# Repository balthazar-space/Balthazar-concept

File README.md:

# Balthazar

Open-hardware laptop computer modules description and concept.

These are electronic schematic modules as presented at https://balthazar.space/wiki/Balthazar
with the main aim for team access.

We are building it from periphery - inwards.

## Repositories

### BalthazarPSU

[BalthazarPSU](https://github.com/balthazar-space/balthazarPSU3) is a combined battery charger, buck-boost coverter and stereo power amplifier.

Previous versions:
   - [Version 2](https://github.com/balthazar-space/balthazarPSU2)
   - [Version 1](https://github.com/balthazar-space/balthazarPSU)

### BalthazarKeyboard
[BalthazarKeyboard](https://github.com/balthazar-space/balthazarKeyboard3) is a somewhat simplified ergonomic computer keyboard with a "diy" approach. The second iteration of the updated keyboard has some more geometric consistency. The third version adds OLED support and a menu for password protecting bootup and choosing a boot target (actual booting is still WIP).

QMK based firmware can be found in [BalthazarKeyboardQMK](https://github.com/balthazar-space/balthazarKeyboardQMK)

Previous versions:
   - [Version 2](https://github.com/balthazar-space/balthazarKeyboard2)
   - [Version 1](https://github.com/balthazar-space/balthazarKeyboard)

### BalthazarIO
[BalthazarIO](https://github.com/balthazar-space/balthazarIO) is a simple USB2.0 four-port hub for the internal devices:
   keyboard and touchpad (optional trackpad), webcam and optional audiocard.

### Case and design

[Case and design](https://github.com/balthazar-space/case-and-design) contains drawings, in DXF, DWG and STL formats.

### Unifying-PCB

[Unifying-PCB](https://github.com/balthazar-space/Unifying-PCB) is a single PCB solution for connecting the three previously designed Balthazar modules (I/O, power supply, USB 2.0, 3.0 controllers, keyboard and adding Compute Module compatible FPGA boards. 

## Prototype

So, far no prototype was built yet - these are preliminary files to be checked in practise, however the progress and pictures of the first pre-prototype are to be seen on our https://balthazar.space website under the News and Specifications and all over (also, many pretty pictures there and user-case scenarios).

Some philosophy is in the .pdf files included. The newest is [.pdf number 3](./Balthazar_System03.pdf).

## License

All resources licensed under the CERN Open Hardware Licence CERN-OHL W V.2.0

Version 2.0 of the CERN-OHL introduces three variants of the licence – strongly (S) reciprocal, weakly (W) reciprocal and permissive (P) – which aim to address specific constraints caused by different collaboration models currently used in open-hardware projects. 

The first two variants mean that if any product is made using an open hardware design, the design of that product, including any improvements or modifications, should be made available under the same licence as that of the original product. Permissive licences do not impose this condition.

See the [LICENSE.md](./LICENSE.md) file for more information.

## Funding

This project is funded through the [NGI Zero Entrust Fund](https://nlnet.nl/entrust), a fund
established by [NLnet](https://nlnet.nl) with financial support from the European Commission's
[Next Generation Internet](https://ngi.eu) program. Learn more on the [NLnet project page](https://nlnet.nl/project/Balthazar-Casing/).

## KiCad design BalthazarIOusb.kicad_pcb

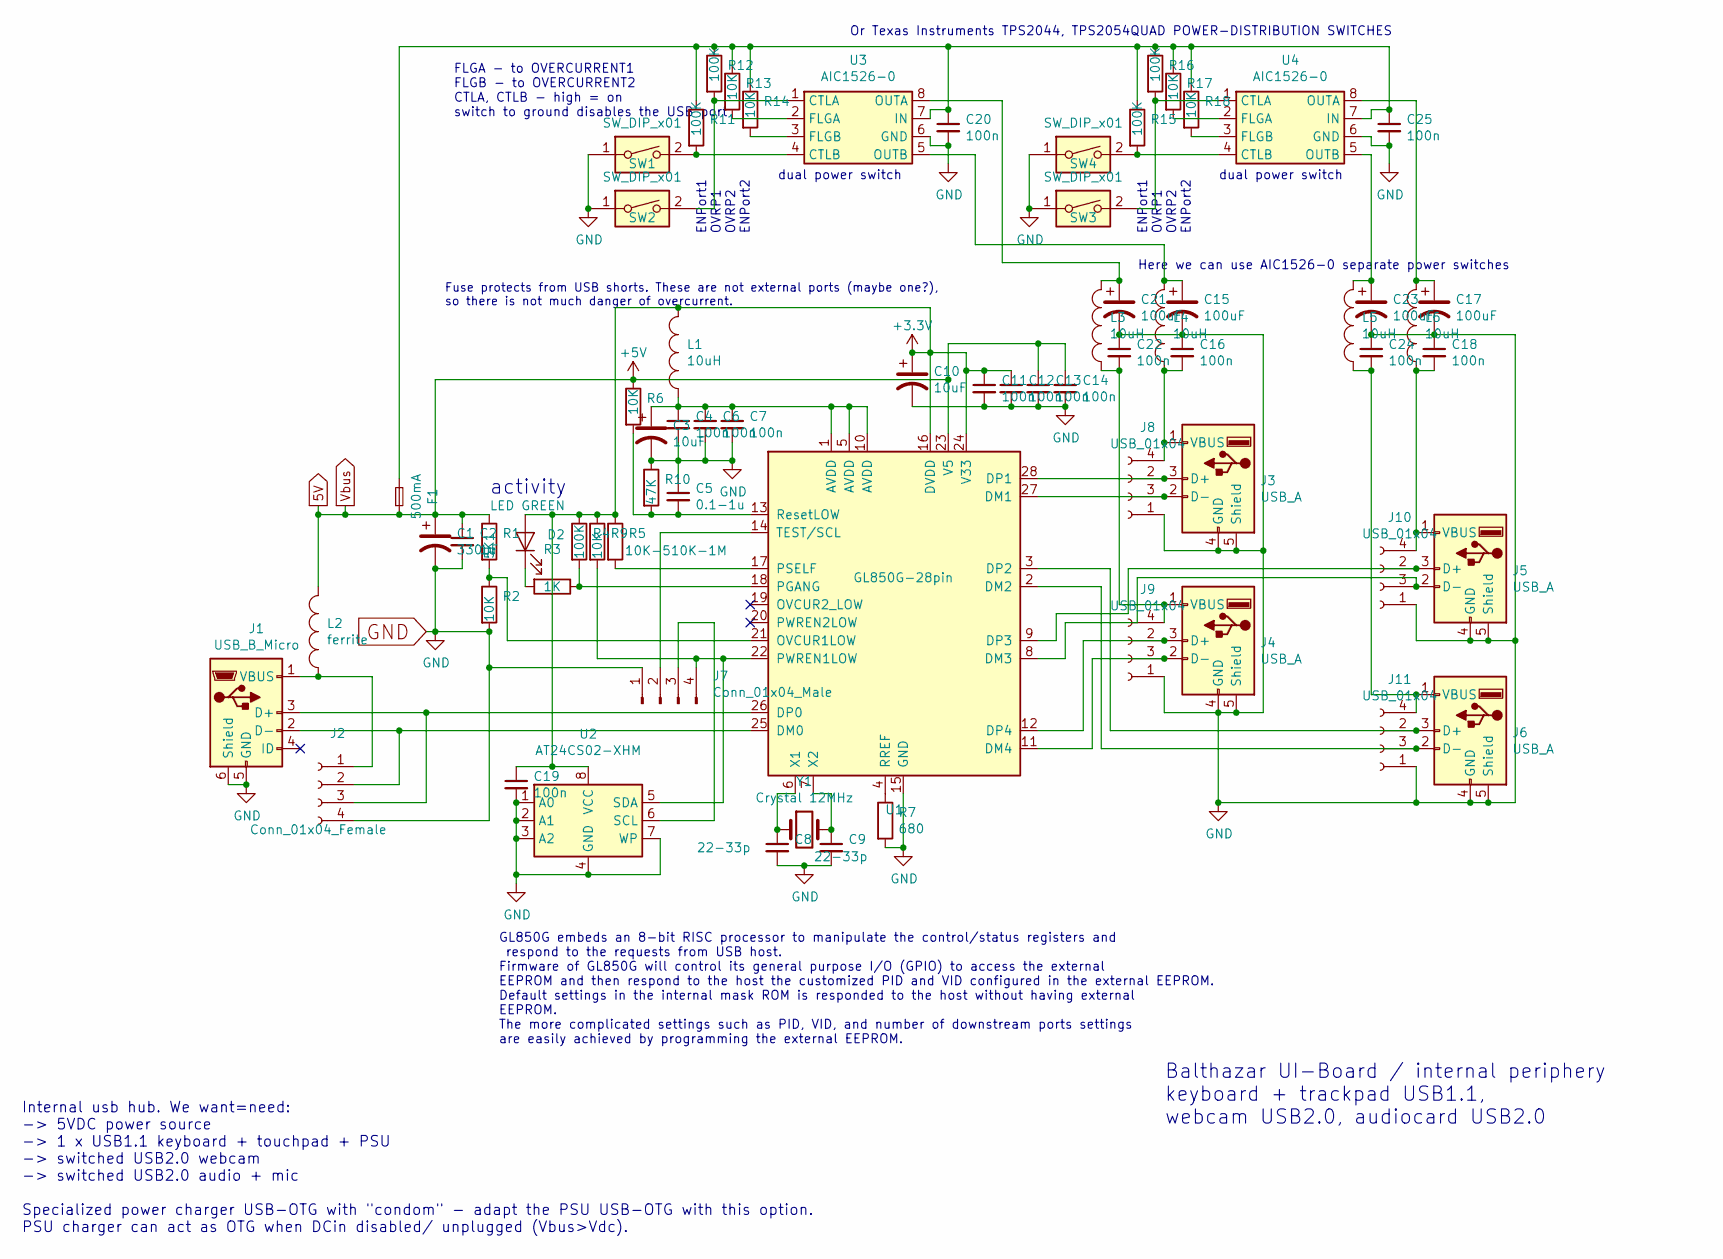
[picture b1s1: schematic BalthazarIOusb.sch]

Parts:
C1: 330uF; CP_Radial_D8.0mm_P2.50mm
C2: 1u; C_1206_3216Metric
C3, C10: 10uF; C_1206_3216Metric
C4, C6, C7, C11, C12, C13, C14, C16, C18, C19, C20, C22, C24, C25: 100n; C_1206_3216Metric
C5: 0.1-1u; C_1206_3216Metric
C8, C9: 22-33p; C_1206_3216Metric
C15, C17, C21, C23: 100uF; CP_Radial_D6.3mm_P2.50mm
D2: LED GREEN; LED_1206_3216Metric
F1: 500mA; Fuse_1206_3216Metric
J1: USB_B_Micro; USB_Micro-AB_Molex_47590-0001
J2: Conn_01x04_Female; PinSocket_1x04_P2.54mm_Horizontal
J3, J4, J5, J6: USB_A; USB_A_CNCTech_1001-011-01101_Horizontal
J7: Conn_01x04_Male; PinHeader_1x04_P2.54mm_Horizontal
J8, J9, J10, J11: USB_01x04; PinSocket_1x04_P2.54mm_Horizontal
L1, L3, L4, L5, L6: 10uH; L_1206_3216Metric
L2: ferrite; L_1206_3216Metric
R1: 5K1; R_1206_3216Metric
R2, R6, R9, R13, R14, R17, R18: 10K; R_1206_3216Metric
R3: 1K; R_1206_3216Metric
R4, R11, R12, R15, R16: 100K; R_1206_3216Metric
R5: 10K-510K-1M; R_1206_3216Metric
R7: 680; R_1206_3216Metric
R10: 47K; R_1206_3216Metric
SW1, SW2, SW3, SW4: SW_DIP_x01; SW_DIP_SPSTx01_Slide_9.78x4.72mm_W7.62mm_P2.54mm
U1: GL850G-28pin; SSOP-28_5.3x10.2mm_P0.65mm
U2: AT24CS02-XHM; SOP-8_3.9x4.9mm_P1.27mm
U3, U4: AIC1526-0; SOP-8_3.9x4.9mm_P1.27mm
Y1: Crystal 12MHz; Crystal_HC50_Vertical

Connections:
5V: C1.1, C2.1, C13.1, C14.1, F1.1, L2.2, R1.1, R6.1, U1.23 (V5)
+3V3: C10.1, C11.1, C12.1, C19.1, D2.2 (A), L1.2, R4.1, R5.1, R9.1, U1.16 (DVDD), U1.24 (V33), U2.8 (VCC)
GND: C1.2, C2.2, C3.2, C4.2, C5.1, C6.2, C7.2, C8.2, C9.2, C10.2, C11.2, C12.2, C13.2, C14.2, C15.2, C16.1, C17.2, C18.1, C19.2, C20.2, C21.2, C22.1, C23.2, C24.1, C25.2, J1.5 (GND), J1.6 (Shield), J2.4, J3.4 (GND), J3.5 (Shield), J4.4 (GND), J4.5 (Shield), J5.4 (GND), J5.5 (Shield), J6.4 (GND), J6.5 (Shield), J7.1, J8.1 (Vbus), J9.1 (Vbus), J10.1 (Vbus), J11.1 (Vbus), R2.2, R7.2, R10.1, SW1.1, SW2.1, SW3.1, SW4.1, U1.15 (GND), U2.1 (A0), U2.2 (A1), U2.3 (A2), U2.4 (GND), U2.7 (WP), U3.6 (GND), U4.6 (GND)
unnamed: C3.1, C4.1, C6.1, C7.1, L1.1, U1.1 (AVDD), U1.5 (AVDD), U1.10 (AVDD)
unnamed: C5.2, R6.2, R10.2, U1.13 (ResetLOW)
unnamed: C8.1, U1.6 (X1), Y1.1
unnamed: C9.1, U1.7 (X2), Y1.2
unnamed: C15.1, L4.2, U3.5 (OUTB)
unnamed: C16.2, J3.1 (VBUS), J8.4 (gnd), L4.1
unnamed: C17.1, L6.2, U4.8 (OUTA)
unnamed: C18.2, J5.1 (VBUS), J10.4 (gnd), L6.1
unnamed: C20.1, C25.1, F1.2, R11.1, R12.1, R13.1, R14.1, R15.1, R16.1, R17.1, R18.1, U3.7 (IN), U4.7 (IN)
unnamed: C21.1, L3.2, U3.8 (OUTA)
unnamed: C22.2, J4.1 (VBUS), J9.4 (gnd), L3.1
unnamed: C23.1, L5.2, U4.5 (OUTB)
unnamed: C24.2, J6.1 (VBUS), J11.4 (gnd), L5.1
unnamed: D2.1 (K), R3.2
unnamed: J1.1 (VBUS), J2.1, L2.1
unnamed: J1.2 (D-), J2.2, U1.25 (DM0)
unnamed: J1.3 (D+), J2.3, U1.26 (DP0)
unnamed: J3.2 (D-), J8.3, U1.27 (DM1)
unnamed: J3.3 (D+), J8.2, U1.28 (DP1)
unnamed: J4.2 (D-), J9.3, U1.11 (DM4)
unnamed: J4.3 (D+), J9.2, U1.12 (DP4)
unnamed: J7.2, U1.14 (TEST/SCL)
unnamed: J7.3, U2.6 (SCL)
unnamed: J7.4, R9.2, U1.22 (PWREN1LOW), U2.5 (SDA)
unnamed: J5.3 (D+), J10.2, U1.9 (DP3)
unnamed: J5.2 (D-), J10.3, U1.8 (DM3)
unnamed: J6.3 (D+), J11.2, U1.3 (DP2)
unnamed: J6.2 (D-), J11.3, U1.2 (DM2)
unnamed: R1.2, R2.1, U1.21 (OVCUR1LOW)
unnamed: R3.1, R4.2, U1.18 (PGANG)
unnamed: R5.2, U1.17 (PSELF)
unnamed: R7.1, U1.4 (RREF)
unnamed: R11.2, SW1.2, U3.4 (CTLB)
unnamed: R12.2, SW2.2, U3.1 (CTLA)
unnamed: R13.2, U3.2 (FLGA)
unnamed: R14.2, U3.3 (FLGB)
unnamed: R15.2, SW4.2, U4.4 (CTLB)
unnamed: R16.2, SW3.2, U4.1 (CTLA)
unnamed: R17.2, U4.2 (FLGA)
unnamed: R18.2, U4.3 (FLGB)

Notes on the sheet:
Balthazar UI-Board / internal periphery keyboard + trackpad USB1.1, webcam USB2.0, audiocard USB2.0
Fuse protects from USB shorts. These are not external ports (maybe one?), so there is not much danger of overcurrent.
activity
Internal usb hub. We want=need: -> 5VDC power source -> 1 x USB1.1 keyboard + touchpad + PSU -> switched USB2.0 webcam -> switched USB2.0 audio + mic Specialized power charger USB-OTG with "condom" - adapt the PSU USB-OTG with this option. PSU charger can act as OTG when DCin disabled/ unplugged (V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
Here we can use AIC1526-0 separate power switches
ENPort1 OVRP1 OVRP2 ENPort2
dual power switch
Or Texas Instruments TPS2044, TPS2054QUAD POWER-DISTRIBUTION SWITCHES
FLGA - to OVERCURRENT1 FLGB - to OVERCURRENT2 CTLA, CTLB - high = on switch to ground disables the USB port
GL850G embeds an 8-bit RISC processor to manipulate the control/status registers and respond to the requests from USB host. Firmware of GL850G will control its general purpose I/O (GPIO) to access the external EEPROM and then respond to the host the customized PID and VID configured in the external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

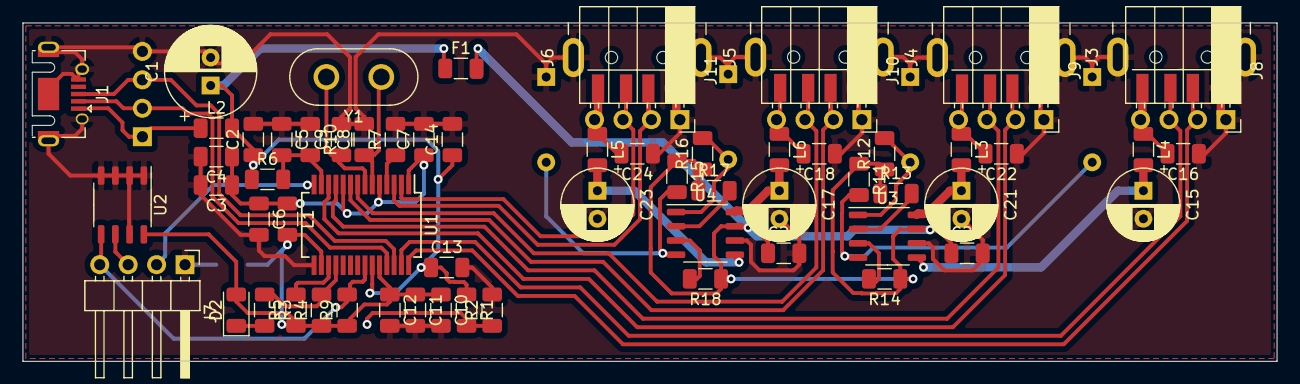
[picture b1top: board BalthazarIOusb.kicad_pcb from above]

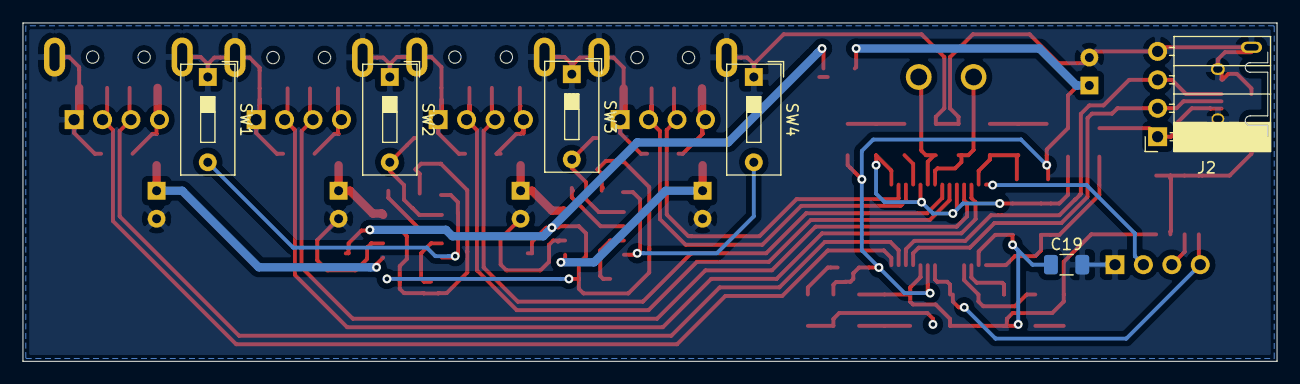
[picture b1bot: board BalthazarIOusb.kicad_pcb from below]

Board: 2 copper layers, 112.0 x 30.2 mm, 70 parts (6 on the bottom side), 43 nets.

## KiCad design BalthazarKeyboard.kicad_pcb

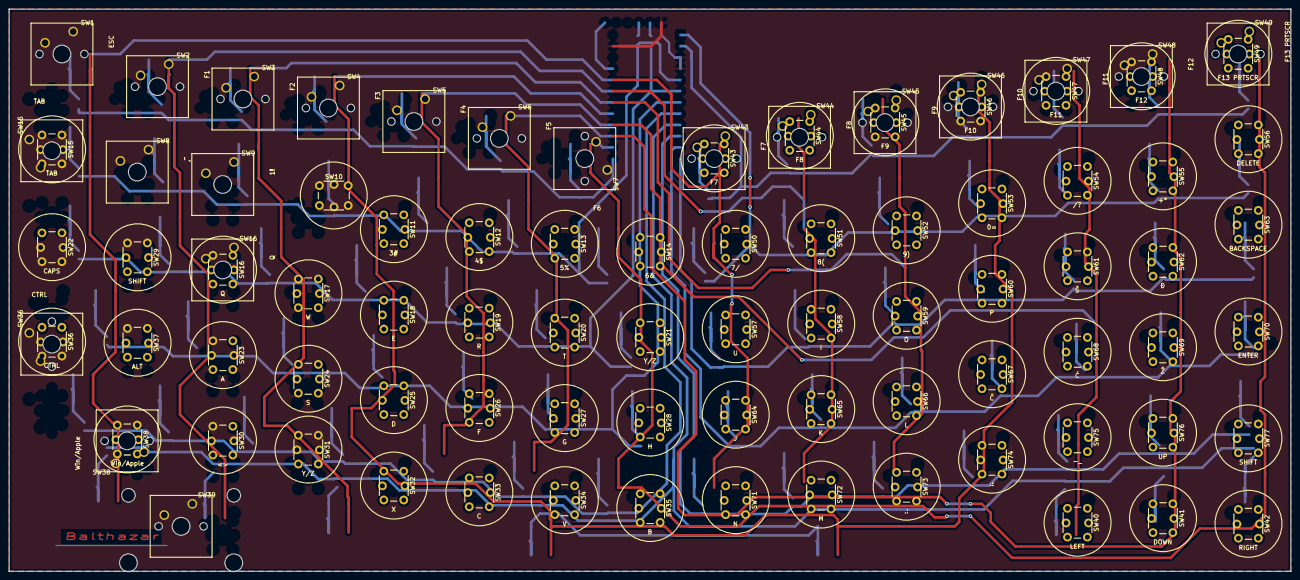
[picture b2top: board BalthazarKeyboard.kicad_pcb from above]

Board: 2 copper layers, 289.6 x 127.0 mm, 88 parts (0 on the bottom side), 18 nets.

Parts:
SW1: ESC; SW_Cherry_MX_1.25u_PCB
SW2: F1; SW_Cherry_MX_1.00u_PCB
SW3: F2; SW_Cherry_MX_1.00u_PCB
SW4: F3; SW_Cherry_MX_1.00u_PCB
SW5: F4; SW_Cherry_MX_1.00u_PCB
SW6: F5; SW_Cherry_MX_1.00u_PCB
SW7: F6; SW_Cherry_MX_1.00u_PCB
SW8: ¸¨; SW_Cherry_MX_1.00u_Plate
SW9: 1!; SW_Cherry_MX_1.00u_Plate
SW10: 2; SW_Cherry_MX_1.00u_Plate
SW11: 3#; SW_PUSH_6mm_8mm
SW12: 4$; SW_PUSH_6mm_8mm
SW13: 5%; SW_PUSH_6mm_8mm
SW14: 6&; SW_PUSH_6mm_8mm
SW15: TAB; SW_Cherry_MX_1.25u_Plate
SW15#2: TAB; SW_PUSH_6mm_8mm
SW16: Q; SW_Cherry_MX_1.00u_Plate
SW16#2: Q; SW_PUSH_6mm_8mm
SW17: W; SW_PUSH_6mm_8mm
SW18: E; SW_PUSH_6mm_8mm
SW19: R; SW_PUSH_6mm_8mm
SW20: T; SW_PUSH_6mm_8mm
SW21, SW31: Y/Z; SW_PUSH_6mm_8mm
SW22: CAPS; SW_PUSH_6mm_8mm
SW23: A; SW_PUSH_6mm_8mm
SW24: S; SW_PUSH_6mm_8mm
SW25: D; SW_PUSH_6mm_8mm
SW26: F; SW_PUSH_6mm_8mm
SW27: G; SW_PUSH_6mm_8mm
SW28: H; SW_PUSH_6mm_8mm
SW29, SW77: SHIFT; SW_PUSH_6mm_8mm
SW30: <>; SW_PUSH_6mm_8mm
SW32: X; SW_PUSH_6mm_8mm
SW33: C; SW_PUSH_6mm_8mm
SW34: V; SW_PUSH_6mm_8mm
SW35: B; SW_PUSH_6mm_8mm
SW36: CTRL; SW_Cherry_MX_1.25u_PCB
SW36#2: CTRL; SW_PUSH_6mm_8mm
SW37: ALT; SW_PUSH_6mm_8mm
SW38: Win/Apple; SW_Cherry_MX_1.25u_PCB
SW38#2: Win/Apple; SW_PUSH_6mm_8mm
SW39: SPACE; SW_Cherry_MX_2.00u_PCB
SW40: LEFT; SW_PUSH_6mm_8mm
SW41: DOWN; SW_PUSH_6mm_8mm
SW42: RIGHT; SW_PUSH_6mm_8mm
SW43: F7; SW_Cherry_MX_1.00u_PCB
SW43#2: F7; SW_PUSH_6mm_8mm
SW44: F8; SW_Cherry_MX_1.00u_PCB
SW44#2: F8; SW_PUSH_6mm_8mm
SW45: F9; SW_Cherry_MX_1.00u_PCB
SW45#2: F9; SW_PUSH_6mm_8mm
SW46: F10; SW_Cherry_MX_1.00u_PCB
SW46#2: F10; SW_PUSH_6mm_8mm
SW47: F11; SW_Cherry_MX_1.00u_PCB
SW47#2: F11; SW_PUSH_6mm_8mm
SW48: F12; SW_Cherry_MX_1.00u_PCB
SW48#2: F12; SW_PUSH_6mm_8mm
SW49: F13 PRTSCR; SW_Cherry_MX_1.25u_PCB
SW49#2: F13 PRTSCR; SW_PUSH_6mm_8mm
SW50: 7/; SW_PUSH_6mm_8mm
SW51: 8(; SW_PUSH_6mm_8mm
SW52: 9); SW_PUSH_6mm_8mm
SW53: 0=; SW_PUSH_6mm_8mm
SW54: /?; SW_PUSH_6mm_8mm
SW55: +*; SW_PUSH_6mm_8mm
SW56: DELETE; SW_PUSH_6mm_8mm
SW57: U; SW_PUSH_6mm_8mm
SW58: I; SW_PUSH_6mm_8mm
SW59: O; SW_PUSH_6mm_8mm
SW60: P; SW_PUSH_6mm_8mm
SW61: Š; SW_PUSH_6mm_8mm
SW62: Đ; SW_PUSH_6mm_8mm
SW63: BACKSPACE; SW_PUSH_6mm_8mm
SW64: J; SW_PUSH_6mm_8mm
SW65: K; SW_PUSH_6mm_8mm
SW66: L; SW_PUSH_6mm_8mm
SW67: Č; SW_PUSH_6mm_8mm
SW68: Ć; SW_PUSH_6mm_8mm
SW69: Ž; SW_PUSH_6mm_8mm
SW70: ENTER; SW_PUSH_6mm_8mm
SW71: N; SW_PUSH_6mm_8mm
SW72: M; SW_PUSH_6mm_8mm
SW73: ,;; SW_PUSH_6mm_8mm
SW74: .:; SW_PUSH_6mm_8mm
SW75: -_; SW_PUSH_6mm_8mm
SW76: UP; SW_PUSH_6mm_8mm

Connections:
unnamed: SW15.2, SW15#2.2
unnamed: SW16.2, SW16#2.2
unnamed: SW36.2, SW36#2.2
unnamed: SW38.2, SW38#2.2
unnamed: SW43.2, SW43#2.2
unnamed: SW44.2, SW44#2.2
unnamed: SW45.2, SW45#2.2
unnamed: SW46.2, SW46#2.2
unnamed: SW47.2, SW47#2.2
unnamed: SW48.2, SW48#2.2
unnamed: SW49.2, SW49#2.2
row1: SW1.1, SW8.1, SW15.1, SW15#2.1, SW22.1, SW29.1, SW36.1, SW36#2.1, SW43.1, SW43#2.1, SW50.1, SW57.1, SW64.1, SW71.1
row2: SW2.1, SW9.1, SW16.1, SW16#2.1, SW23.1, SW30.1, SW37.1, SW44.1, SW44#2.1, SW51.1, SW58.1, SW65.1, SW72.1
row3: SW3.1, SW10.1, SW17.1, SW24.1, SW31.1, SW38.1, SW38#2.1, SW45.1, SW45#2.1, SW52.1, SW59.1, SW66.1, SW73.1
row4: SW4.1, SW11.1, SW18.1, SW25.1, SW32.1, SW39.1, SW46.1, SW46#2.1, SW53.1, SW60.1, SW67.1, SW74.1
row5: SW5.1, SW12.1, SW19.1, SW26.1, SW33.1, SW40.1, SW47.1, SW47#2.1, SW54.1, SW61.1, SW68.1, SW75.1
row6: SW6.1, SW13.1, SW20.1, SW27.1, SW34.1, SW41.1, SW48.1, SW48#2.1, SW55.1, SW62.1, SW69.1, SW76.1
row7: SW7.1, SW14.1, SW21.1, SW28.1, SW35.1, SW42.1, SW49.1, SW49#2.1, SW56.1, SW63.1, SW70.1, SW77.1

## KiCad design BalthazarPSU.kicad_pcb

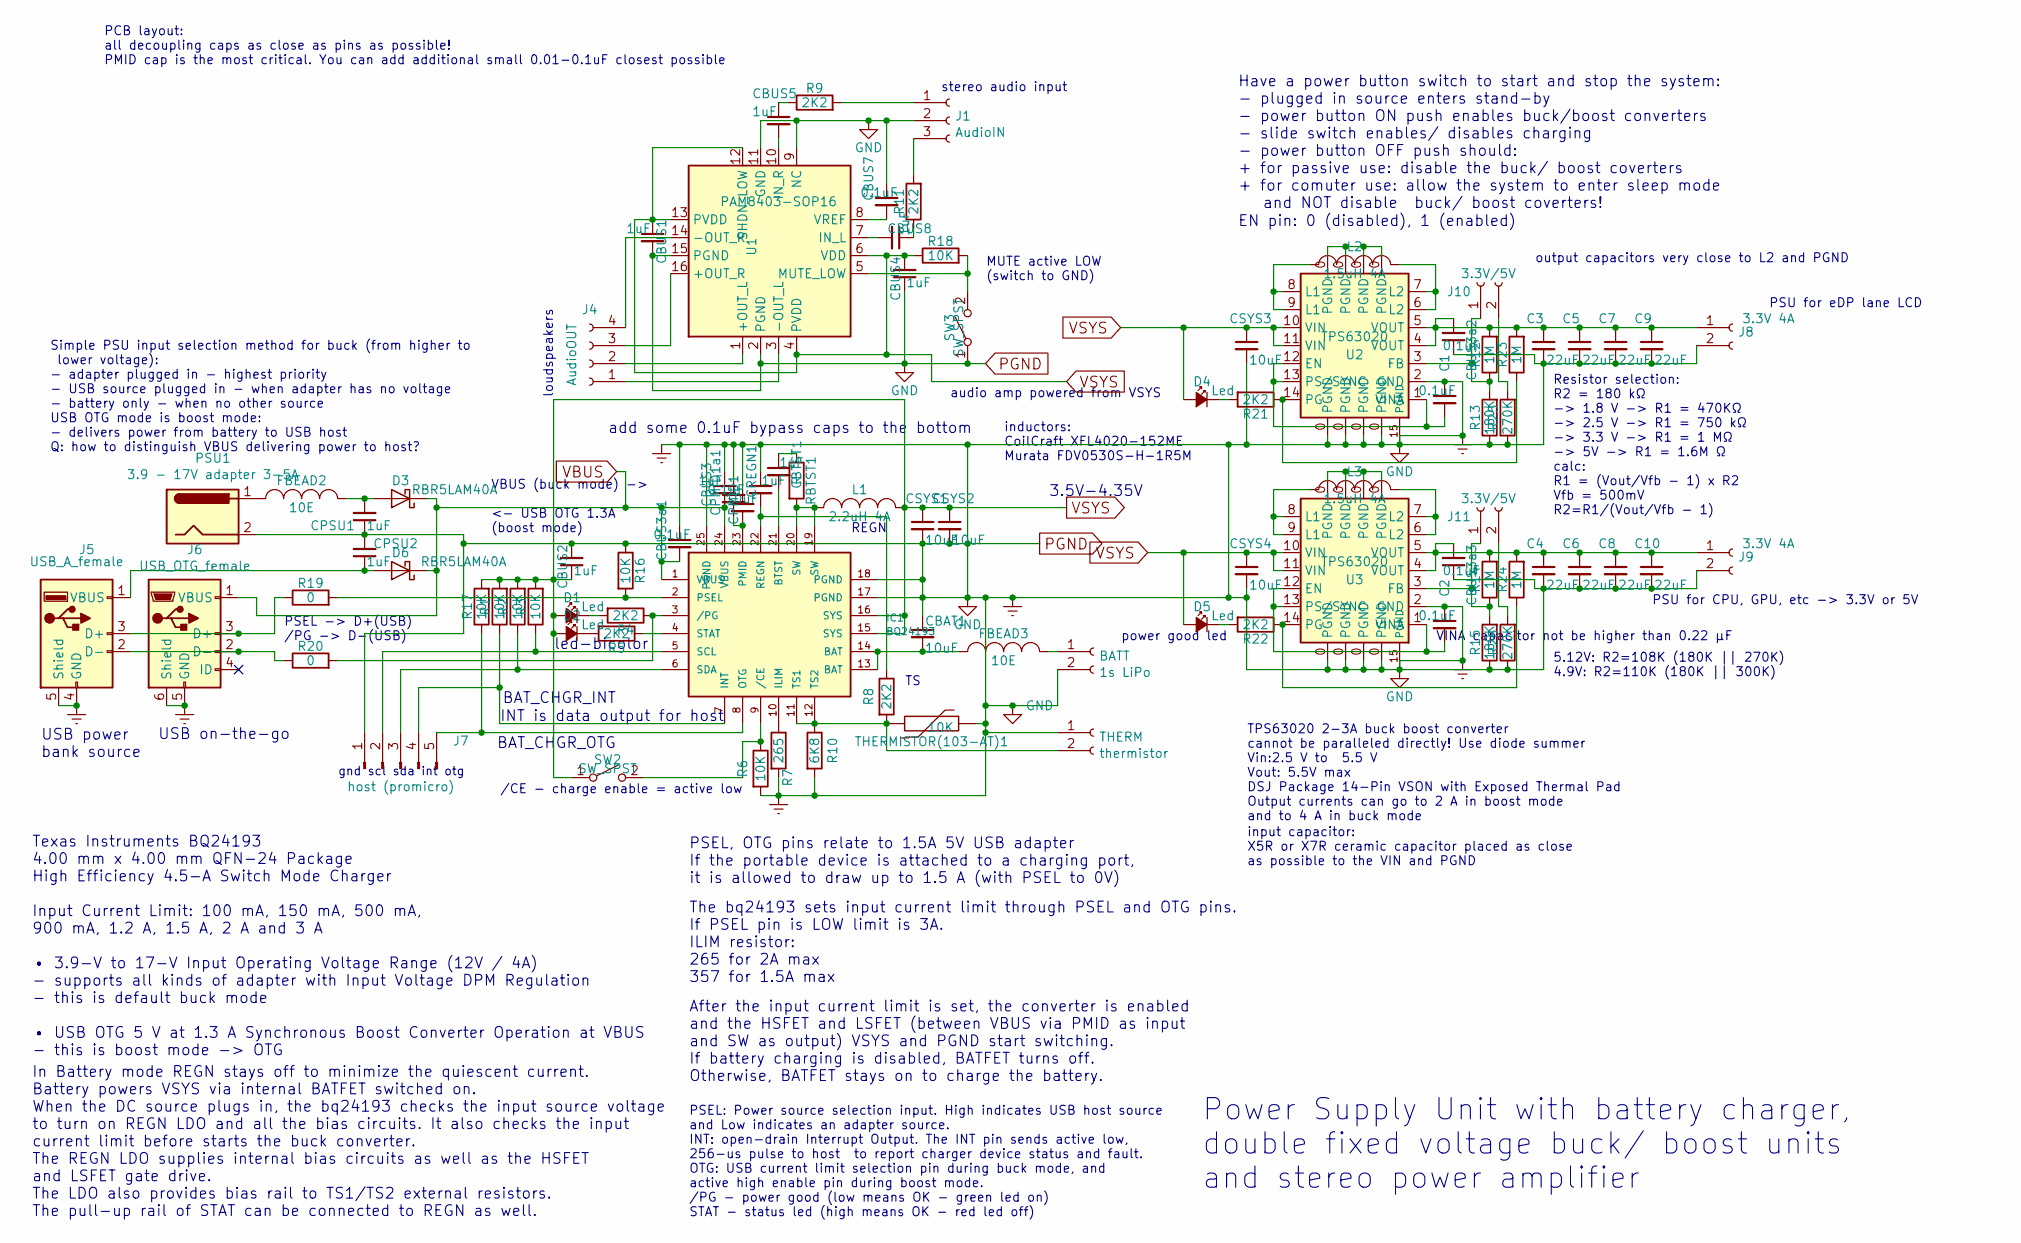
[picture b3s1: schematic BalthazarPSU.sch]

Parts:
BATT: 1s LiPo; TerminalBlock_bornier-2_P5.08mm
C1, C2: 0.1uF; C_1206_3216Metric
C3, C4, C5, C6, C7, C8, C9, C10: 22uF; C_1206_3216Metric
CBAT1: 10uF; C_1206_3216Metric
CBTST1: 1uF; C_1206_3216Metric
CBUS1, CBUS2, CBUS3, CBUS4, CBUS5, CBUS8: 1uF; C_1206_3216Metric
CBUS3a1, CBUS3a2, CBUS3a3: 0.1uF; C_0805_2012Metric
CBUS7: 0.1uF; C_1206_3216Metric
CPMID1: 10uF; C_1206_3216Metric
CPMID1a1: 0.1uF; C_0805_2012Metric
CPSU1, CPSU2: 1uF; C_1206_3216Metric
CREGN1: 1uF; C_1206_3216Metric
CSYS1, CSYS2, CSYS3, CSYS4: 10uF; C_1206_3216Metric
D1, D2, D4, D5: Led; LED_1206_3216Metric
D3, D6: RBR5LAM40A; D_SOD-128
FBEAD2, FBEAD3: 10E; L_Neosid_MicroCoil_Ms36-L
IC1: BQ24193; QFN-24-1EP_4x4mm_P0.5mm_EP2.7x2.7mm_ThermalVias
J1: AudioIN; PinSocket_1x03_P2.54mm_Horizontal
J4: AudioOUT; PinSocket_1x04_P2.54mm_Horizontal
J5: USB_A_female; USB_A_CNCTech_1001-011-01101_Horizontal-Female
J6: USB_OTG_female; USB_Micro-B_Molex-105133-0031
J7: host (promicro); PinHeader_1x06_P2.54mm_Horizontal
J8, J9: 3.3V 4A; TerminalBlock_bornier-2_P5.08mm
J10, J11: 3.3V/5V; TestPoint_2Pads_Pitch2.54mm_Drill0.8mm
L1: 2.2uH 4A; L_Coilcraft_XxL4020
L2, L3: 1.5uH 4A; L_Coilcraft_XxL4020
PSU1: 3.9 - 17V adapter 3-5A; TerminalBlock_bornier-2_P5.08mm
R1, R2, R3, R6, R16, R17, R18: 10K; R_1206_3216Metric
R4, R5, R8, R9, R11, R21, R22: 2K2; R_1206_3216Metric
R7: 265; R_1206_3216Metric
R10: 6K8; R_1206_3216Metric
R12, R14, R23, R24: 1M; R_1206_3216Metric
R13, R15: 180K; R_1206_3216Metric
R19, R20: 0; R_1206_3216Metric
R25, R26: 270K; R_1206_3216Metric
RBTST1: R; R_1206_3216Metric
SW2, SW3: SW_SPST; SW_DIP_SPSTx01_Slide_6.7x4.1mm_W7.62mm_P2.54mm_LowProfile
THERM: thermistor; TestPoint_2Pads_Pitch2.54mm_Drill0.8mm
THERMISTOR(103-AT)1: 10K; R_1206_3216Metric
U1: PAM8403-SOP16; SOP-16_4.4x10.4mm_P1.27mm
U2, U3: TPS63020; WSON-14-1EP_4.0x4.0mm_P0.5mm_EP2.6x2.6mmThermalPads

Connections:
unnamed: C1.2, U2.1 (VINA), U2.12 (EN), U2.13 (PS/SYNC)
unnamed: C2.2, U3.1 (VINA), U3.12 (EN), U3.13 (PS/SYNC)
unnamed: C3.1, C5.1, C7.1, C9.1, CBUS3a2.2, J8.1, R12.2, R23.2, U2.4 (VOUT), U2.5 (VOUT)
unnamed 3: C4.1, C6.1, C8.1, C10.1, CBUS3a3.2, J9.1, R14.2, R24.2, U3.4 (VOUT), U3.5 (VOUT); also elsewhere on the board
unnamed: CBAT1.2, FBEAD3.1, IC1.13 (BAT), IC1.14 (BAT)
unnamed: CBTST1.1, RBTST1.1
unnamed: CBTST1.2, IC1.21 (BTST)
unnamed: CBUS5.1, R9.1
unnamed: CBUS5.2, U1.10 (IN_R)
unnamed: CBUS7.2, U1.8 (VREF)
unnamed: CBUS8.1, R11.1
unnamed: CBUS8.2, U1.7 (IN_L)
unnamed: CPMID1.2, CPMID1a1.2, IC1.23 (PMID)
unnamed: CPSU1.2, D3.2 (A), FBEAD2.2
unnamed: CPSU2.1, D6.2 (A), J5.1 (VBUS)
unnamed: CREGN1.2, IC1.22 (REGN), R8.1
unnamed: D1.2 (C), R4.2
unnamed: D2.2 (C), R5.2
unnamed: D4.2 (C), R21.2
unnamed: D5.2 (C), R22.2
unnamed: FBEAD2.1, PSU1.1
unnamed 21: BATT.1, FBEAD3.2; also elsewhere on the board
unnamed: IC1.2 (PSEL), R16.2, R19.2
unnamed: IC1.3 (/PG), R4.1, R20.2
unnamed: IC1.4 (STAT), R5.1
unnamed: IC1.5 (SCL), J7.2, R3.1
unnamed: IC1.6 (SDA), J7.3, R2.1
unnamed: IC1.7 (INT), J7.4, R1.1
unnamed: IC1.8 (OTG), J7.5, R17.1
unnamed: IC1.9 (/CE), R6.1, SW2.2 (B)
unnamed: IC1.10 (ILIM), R7.1
unnamed 31: IC1.11 (TS1), IC1.12 (TS2), R8.2, R10.1, THERM.2, THERMISTOR(103-AT)1.2; also elsewhere on the board
unnamed: IC1.19 (SW), IC1.20 (SW), L1.1, RBTST1.2
unnamed: J1.1, R9.2
unnamed: J1.3, R11.2
unnamed: J4.1, U1.3 (-OUT_L)
unnamed: J4.2, U1.1 (+OUT_L)
unnamed: J4.3, U1.16 (+OUT_R)
unnamed: J4.4, U1.14 (-OUT_R)
unnamed: J5.2 (D-), J6.2 (D-), R20.1
unnamed: J5.3 (D+), J6.3 (D+), R19.1
unnamed: J10.1, R12.1, R13.2, U2.3 (FB)
unnamed: J10.2, R25.2
unnamed: J11.1, R14.1, R15.2, U3.3 (FB)
unnamed: J11.2, R26.2
unnamed: L2.1, U2.8 (L1), U2.9 (L1)
unnamed: L2.2, U2.6 (L2), U2.7 (L2)
unnamed: L3.1, U3.8 (L1), U3.9 (L1)
unnamed: L3.2, U3.6 (L2), U3.7 (L2)
unnamed: R18.2, SW3.2 (B), U1.5 (MUTE_LOW)
unnamed: R21.1, R23.1, U2.14 (PG)
unnamed: R22.1, R24.1, U3.14 (PG)
PGND: BATT.2, C1.1, C2.1, C3.2, C4.2, C5.2, C6.2, C7.2, C8.2, C9.2, C10.2, CBAT1.1, CBUS1.2, CBUS2.2, CBUS3.1, CBUS3a1.1, CBUS3a2.1, CBUS3a3.1, CBUS4.1, CBUS7.1, CPMID1.1, CPMID1a1.1, CPSU1.1, CPSU2.2, CREGN1.1, CSYS1.2, CSYS2.2, CSYS3.2, CSYS4.2, IC1.17 (PGND), IC1.18 (PGND), IC1.25 (PGND), J1.2, J5.4 (GND), J5.5 (Shield), J6.5 (GND), J6.6 (Shield), J7.1, J8.2, J9.2, PSU1.2, R6.2, R7.2, R10.2, R13.1, R15.1, R16.1, R25.1, R26.1, SW3.1 (A), THERM.1, THERMISTOR(103-AT)1.1, U1.2 (PGND), U1.9 (NC), U1.11 (GND), U1.15 (PGND), U2.0 (PGND), U2.2 (GND), U2.15 (PGND), U3.0 (PGND), U3.2 (GND), U3.15 (PGND); also elsewhere on the board
VBUS: CBUS3.2, CBUS3a1.2, D3.1 (K), D6.1 (K), IC1.1 (VBUS), IC1.24 (VBUS), J6.1 (VBUS)
VSYS: CBUS1.1, CBUS2.1, CBUS4.2, CSYS1.1, CSYS2.1, CSYS3.1, CSYS4.1, D1.1 (A), D2.1 (A), D4.1 (A), D5.1 (A), IC1.15 (SYS), IC1.16 (SYS), L1.2, R1.2, R2.2, R3.2, R17.2, R18.1, SW2.1 (A), U1.4 (PVDD), U1.6 (VDD), U1.12 (SHDN_LOW), U1.13 (PVDD), U2.10 (VIN), U2.11 (VIN), U3.10 (VIN), U3.11 (VIN)

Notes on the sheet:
3.5V-4.35V
USB on-the-go
led-bicolor
BAT_CHGR_INT
BAT_CHGR_OTG
INT is data output for host
Texas Instruments BQ24193 4.00 mm x 4.00 mm QFN-24 Package High Efficiency 4.5-A Switch Mode Charger Input Current Limit: 100 mA, 150 mA, 500 mA, 900 mA, 1.2 A, 1.5 A, 2 A and 3 A • 3.9-V to 17-V Input Operating Voltage Range (12V / 4A) - supports all kinds of adapter with Input Voltage DPM Regulat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
PSEL, OTG pins relate to 1.5A 5V USB adapter If the portable device is attached to a charging port, it is allowed to draw up to 1.5 A (with PSEL to 0V)
In Battery mode REGN stays off to minimize the quiescent current. Battery powers VSYS via internal BATFET switched on. When the DC source plugs in, the bq24193 checks the input source voltage to turn on REGN LDO and all the bias circuits. It also checks the input current limit before starts the buc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
The bq24193 sets input current limit through PSEL and OTG pins. If PSEL pin is LOW limit is 3A. ILIM resistor: 265 for 2A max 357 for 1.5A max
After the input current limit is set, the converter is enabled and the HSFET and LSFET (between VBUS via PMID as input and SW as output) VSYS and PGND start switching. If battery charging is disabled, BATFET turns off. Otherwise, BATFET stays on to charge the battery.
PSU for CPU, GPU, etc -> 3.3V or 5V
TPS63020 2-3A buck boost converter cannot be paralleled directly! Use diode summer Vin:2.5 V to 5.5 V Vout: 5.5V max DSJ Package 14-Pin VSON with Exposed Thermal Pad Output currents can go to 2 A in boost mode and to 4 A in buck mode
inductors: CoilCraft XFL4020-152ME Murata FDV0530S-H-1R5M
Resistor selection: R2 = 180 kΩ -> 1.8 V -> R1 = 470KΩ -> 2.5 V -> R1 = 750 kΩ -> 3.3 V -> R1 = 1 MΩ -> 5V -> R1 = 1.6M Ω calc: R1 = (Vout/Vfb - 1) x R2 Vfb = 500mV R2=R1/(Vout/Vfb - 1)
REGN
stereo audio input
loudspeakers
MUTE active LOW (switch to GND)
/CE - charge enable = active low
PSEL: Power source selection input. High indicates USB host source and Low indicates an adapter source. INT: open-drain Interrupt Output. The INT pin sends active low, 256-us pulse to host to report charger device status and fault. OTG: USB current limit selection pin during buck mode, and active h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
PSEL -> D+(USB) /PG -> D-(USB)
Power Supply Unit with battery charger, double fixed voltage buck/ boost units and stereo power amplifier
PCB layout: all decoupling caps as close as pins as possible! PMID cap is the most critical. You can add additional small 0.01-0.1uF closest possible
PSU for eDP lane LCD
audio amp powered from VSYS
VBUS (buck mode) -> <- USB OTG 1.3A (boost mode)
Simple PSU input selection method for buck (from higher to lower voltage): - adapter plugged in - highest priority - USB source plugged in - when adapter has no voltage - battery only - when no other source USB OTG mode is boost mode: - delivers power from battery to USB host Q: how to distinguish 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
output capacitors very close to L2 and PGND
input capacitor: X5R or X7R ceramic capacitor placed as close as possible to the VIN and PGND
VINA capacitor not be higher than 0.22 μF
power good led
5.12V: R2=108K (180K || 270K) 4.9V: R2=110K (180K || 300K)
USB power bank source
gnd scl sda int otg
add some 0.1uF bypass caps to the bottom
EN pin: 0 (disabled), 1 (enabled)
Have a power button switch to start and stop the system: - plugged in source enters stand-by - power button ON push enables buck/boost converters - slide switch enables/ disables charging - power button OFF push should: + for passive use: disable the buck/ boost coverters + for comuter use: allow t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

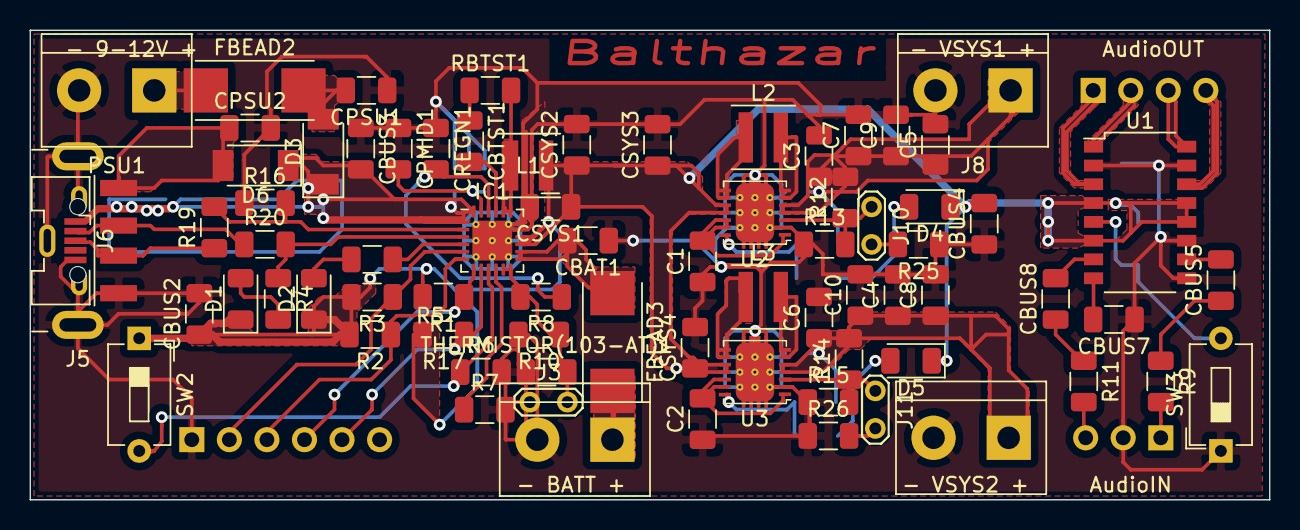
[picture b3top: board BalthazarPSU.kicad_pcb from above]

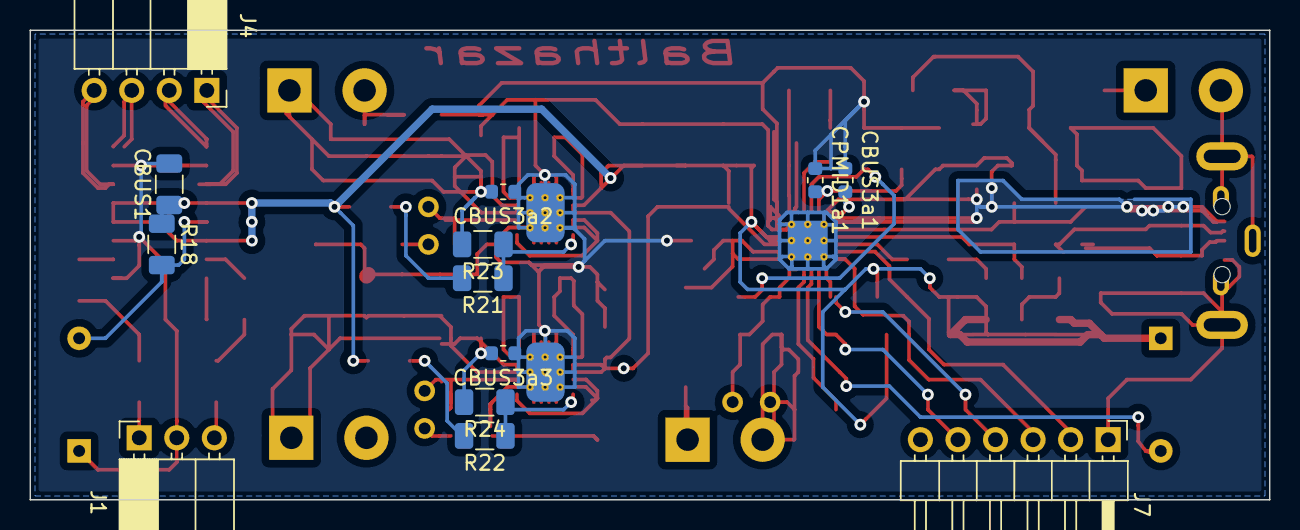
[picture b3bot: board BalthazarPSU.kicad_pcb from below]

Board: 2 copper layers, 83.8 x 31.8 mm, 88 parts (13 on the bottom side), 55 nets.

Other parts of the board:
- BATT +: 1s LiPo; TerminalBlock_bornier-2_P5.08mm
- VSYS2 +: 3.3V 4A; TerminalBlock_bornier-2_P5.08mm
J3: thermistor; TestPoint_2Pads_Pitch2.54mm_Drill0.8mm

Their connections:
unnamed 3: - VSYS2 +.1; also elsewhere on the board
unnamed 21: - BATT +.1; also elsewhere on the board
unnamed 31: J3.2; also elsewhere on the board
PGND: - BATT +.2, - VSYS2 +.2, J3.1; also elsewhere on the board

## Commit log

2020-04-01 Update LICENSE
2020-06-19 NGI0-FSFE: updating license file to include full license text
2021-07-28 admin
2024-06-24 Update README.md
    Keyboard and PSU links
2024-06-25 Readme update, add links, license, consistency
2024-06-26 Update README.md
    Add link to QMK firmware
